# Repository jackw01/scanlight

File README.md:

# A Better Light Source For Scanning Color Negative Film

Left: [scanlight v4](./v4.md), right: [big scanlight](./big.md)

<small>Originally published 2024-08-05, last updated 2026-08-02</small>

## tl;dr

Narrowband trichromatic (RGB) light sources are superior to broadband (white) light for scanning color negative film; there are very good reasons why all commercial film scanners use RGB. ([film scanners were using blue LEDs at least a decade before they would be widely used in consumer products!](https://patents.google.com/patent/JPH09130546A/en?q=(film+scanner+LED)&oq=film+scanner+LED&sort=old)) Scanning film with an RGB light source produces high quality results with minimal post-processing, without the need for specialized software.

### the results

<small>Both scans captured using Fujifilm X-T30. White light scan captured using 95+ CRI 5000K light source. RGB scan captured using custom 450nm+525nm+665nm light source.</small>

## the simplified explanation

Color negative (C-41) film stores an image using cyan, magenta, and yellow dyes. Dyes appear a certain color because they absorb some wavelengths of light; for example, yellow dye mostly absorbs light in the 400-550nm range (which we perceive as violet through green), while allowing other wavelengths (yellow through red) to pass through the film. **These dyes are not intended to produce a human-viewable image, but rather to attenuate certain wavelengths of light for making prints on photosensitive paper.**

White light sources emit light over a broad spectrum of wavelengths. When white light passes through C-41 film, some of these wavelengths are only slightly absorbed by the dyes, which means that these wavelengths aren't useful for recovering the information stored in the individual dye layers - for example, the 580-620nm band (yellow through red-orange light) is mostly transmitted through the film, with a small amount being absorbed by both the magenta and cyan dye layers.

The quality of white light sources is measured with CRI, which represents how well a light source reproduces the true color of a set of standardized color swatches. CRI is effectively a weighted average of how much light a light source emits across different parts of the visible light spectrum, and only a few of these parts matter when it comes to extracting information from color film. **CRI doesn't take into account the deep red (>630nm) and deep blue (<480nm) parts of the spectrum, so as a result, many high-CRI LEDs don't emit much light at these wavelengths, which happen to be where the yellow and cyan dyes absorb the most light.**

<small>note: Standardized scores that take into account these wavelength bands at the edges of the visible spectrum do exist (R9 and R12), but are not readily provided by all LED manufacturers.</small>

With darkroom printing, this is not an issue, as RA-4 color print paper (and motion picture print film) are, by design, most sensitive to specific bands of wavelengths that avoid the crosstalk regions between the dye layers in negative film, and the paper is exposed with an incandescent light source with a smooth emission spectrum across the entire visible range (400-700nm) and beyond.

What about scanning film with a digital camera? Digital camera sensors are designed to capture light in a way that allows for a faithful reproduction of the colors that humans would perceive (this is a gross oversimplification.) C-41 film was *not* designed to be directly viewed by humans.

Not only is the camera sensitive to wavelengths of light that are effectively ignored by RA-4 paper, there is significant crosstalk between the color channel sensitivities of digital camera sensors: light in the ~580-600nm range is seen roughly equally by the red and green channels, and light in the ~480-500nm range is seen by both the green and blue channels.

The red channel of the scan will contain not just information from the red-blocking cyan dye, but also the green-blocking magenta dye. The green channel will contain information from all three dye layers. Additionally, the overall light transmission of C-41 film is heavily biased towards yellow and orange wavelengths due to the orange mask and the relatively large gap between the magenta and cyan dye absorption peaks, which means that **a lot** of light gets through that interferes with both the red and green channels in the camera sensor without carrying much useful information about the colors stored in the film.

<small>note: the orange color of C-41 film is often misunderstood to be the color of the plastic film base, or an orange tint evenly applied over the whole image. It is actually a corrective mask made up of blue- and green-blocking positive images which compensate for deficiencies in the red-sensing and green-sensing layers of the film. For a good explanation of how this works, see [this article](https://observablehq.com/@dorskyee/understanding-color-film). In practice, this means that less-exposed parts of the negative let through disproportionately more yellow, orange, and red light.</small>

So if you scan color negative film with white light, you can't just invert the colors and expect a good result. You need to do some math to try to recover the individual dye layers of the film from ambiguous input data. This can't be done in standard image editing software, which is why dedicated software for negative conversion exists. The level of crosstalk on each channel depends heavily on both the emission spectra of the light source and the spectral sensitivity of the camera, so the conversion process needs to be either calibrated, manually adjusted until it looks “right”, or deduced by the processing software with varying degrees of accuracy. The color depth of the resulting positive image will be relatively low because much of the information recorded by the camera is effectively useless yellow-orange light that has passed through the film without being significantly attenuated by any of the dyes.

To avoid these issues, (almost?) all commercial negative film scanners use a trichromatic narrowband light source with red, green, and blue LEDs to minimize crosstalk between the dye layers in the film and the color channels on the image sensor, and some use monochrome sensors to eliminate sensor crosstalk entirely. When doing it this way, no guesswork is needed to recover a usable image and it's really as simple as inverting the color channels and setting the color balance and black/white points. There is still some crosstalk between camera sensor channels, but now that the light source emits light in three narrow, independently controllable wavelength bands, it can be easily measured and compensated for, or it can be avoided completely by imaging the red, green, and blue channels separately.

### what light source works the best?

When considering the limitations of digital camera sensors, the ideal wavelengths are >650nm for red and <450nm for blue, as shown in the diagram above. Ideally, the green wavelength is 540-560nm to match the absorption peak of the magenta dye, but LEDs in that range are just not practical (see FAQ below for more details), and the standard 525nm works very well.

The next best alternative is to use general purpose RGB LEDs, which typically use 620-630nm for red and 460-480nm for blue. The results will not be the absolute best possible, but will still be far better than with white light. The Fuji Frontier SP3000, a popular professional scanner, uses 630nm for red and 465nm for blue ([source](https://discuss.pixls.us/t/input-color-profile-to-use-for-negatives/20271/13)), but it does not have to contend with the color channel sensitivity of a typical digital camera - it has a monochrome image sensor and combines three exposures taken with red, green, and blue light.

To get the best possible results, I designed my own custom RGB light sources using 665nm red and 455nm blue LEDs. More information on the designs can be found [here (scanlight v4)](./v4.md) and [here (big scanlight)](./big.md). Both light sources allow for individual control of the red, green, and blue channels via a web app. Color balance can be adjusted for single-exposure scanning, and the light can automatically switch colors and trigger a camera to simplify the process of capturing separate exposures for each channel.

All design files for the light sources and film carriers, both current and older versions, can be downloaded from the [GitHub repository](https://github.com/jackw01/scanlight/).

### more sample scans

All scans were processed in [NegPy](https://github.com/marcinz606/NegPy), leaving all settings at the default values. The RGB scans were scanned as **single exposures with all color channels** and sensor crosstalk calibration was applied. The groups of four negatives were scanned and manually processed together in order to demonstrate how the light source affects the overall look of the scans rather than to show a subjectively ideal edit for each photo.

<p align="center"><small>Kodak Ektar 100 (left: white light, right: narrowband RGB light)</small></p>

<p align="center"><small>Fuji 200 (left: white light, right: narrowband RGB light)</small></p>

<p align="center"><small>Kodak Ektar 100 (left: white light, right: narrowband RGB light)</small></p>

<p align="center"><small>Kodak Vision3 500T (left: white light, right: narrowband RGB light)</small></p>

<p align="center"><small>Fuji 200 (left: white light, right: narrowband RGB light)</small></p>

<p align="center"><small>Fuji 200 (left: white light, right: narrowband RGB light)</small></p>

### recommended reading, if you're curious

* Edward J Giorgianni and Thomas E Madden, *Digital Color Management: Encoding Solutions, 2nd Edition*
* Robert L Shanebrook, *Making Kodak Film*

## part 2: responses to frequent questions and comments

<small>Updated 2026-08-02</small>

#### how should i process my scans?
As of 2026, free and open-source film scan processing software exists ([NegPy](https://github.com/marcinz606/NegPy)) which produces excellent results with little effort when inverting single-exposure RGB scans. NegPy uses a processing pipeline which emulates the RA-4 printing process, and supports flat-field correction and automatic merging of trichromatic (separate exposures for red, green, and blue) scans. I would highly recommend this to anyone who is looking to start scanning film at home or is having difficulty with their current processing workflow.

Using software specifically designed for processing white light scans (e.g. Negative Lab Pro) to process RGB scans may give suboptimal results. It's also possible to get good results without using any specialized software, by manually inverting your scans in photo editing software as described below. Manual inversion is much easier with RGB scans than with white light scans, but it still takes more effort than NegPy, and compensating for camera sensor crosstalk may be difficult depending on which image editing software you use.

#### but can't i just edit the white light scan to look like the RGB scan?
You can't get the exact same colors as the RGB scan by adjusting the white balance or individual color channels of a white light scan. This is physically impossible because the light interacted with the film in a fundamentally different way in the white light scan vs. the RGB scan before it was reduced to three bins of wavelengths approximately representing red, green, and blue by the camera sensor; some of the color information stored in the film is lost in this process.

#### but i keep seeing/hearing that using RGB light results in oversaturation or hue shifts
Increasing saturation is often done on purpose to produce a visually striking and not entirely accurate demonstration of why RGB is better (in practice, the differences in color reproduction are more subtle once saturation is equalized), or is the result of processing RGB scans with processing workflows intended to produce normal-looking results with white light scans. No one is saying you can’t adjust saturation in post, or use processing software that produces less-saturated results. Hue shifts are a result of using a processing workflow that doesn't compensate for camera sensor channel crosstalk, and should be a complete non-issue if using the sensor calibration tool in NegPy.

<p align="center"><small>From left to right: RGB scan without sensor calibration (note blue-to-cyan and orange-to-magenta shifts); RGB scan with sensor calibration; Noritsu HS-1800 lab scan</small></p>

#### but the colors in the sample scans still don't look good to me / the colors don't look the way i think film should look
Getting the desired colors from C-41 film, whether by darkroom printing or scanning and editing, has always involved some level of manual adjustment. It is also worth noting that our collective idea of how film is supposed to look is often influenced by highly edited or low-quality scans; old, faded prints; or even software emulations. **Photography is art, and as such it has always involved making subjective decisions about how images should look; all photos are interpretations of raw data and it's up to the photographer to decide what interpretation looks best.** The best starting point for editing is a scan that represents the image data stored in the dye layers of the film with maximum dynamic range and minimal crosstalk.

#### won't this make all film look the same?
Scanning film with RGB light does not neutralize the differences in the "look" of different films; actually, it should produce results that are closer to the intended look of the film when printed on RA-4 paper. The differences in look come from differences in the film's sensitivity to light during exposure and chemical reactions that affect how the dyes are formed during development, not the absorption characteristics of the dyes themselves.

#### should i capture three separate exposures for each color channel?
You can either capture a single image with the red, green, and blue channels on at the same time or capture separate images for each color and merge them later. Both methods can produce satisfactory results. The latter approach has the potential for more technically accurate colors as it eliminates any chance of crosstalk between color channels, but takes significantly more work than capturing a single RGB image which can be processed directly.

When capturing red, green, and blue at the same time, the severity of crosstalk depends heavily on the spectral response of the camera's image sensor and camera manufacturer's color profile, and it may not even be noticeable in many cases. Crosstalk typically manifests as consistent color shifts (usually, reds appearing too pink or greens appearing too yellow,) and can usually be resolved by post-processing with software that supports a crosstalk matrix or RGB primary calibration, such as NegPy (open-source) or Lightroom.

#### how should i adjust the red/green/blue channel levels on the light source?
The red, green, and blue channels on the light source should be adjusted to maximize how much of the camera's dynamic range is utilized on all three color channels. To do this, set the camera white balance to neutral/5000K and adjust the light source so that the histogram peaks on each channel become aligned when the camera is viewing the light through an unexposed, developed piece of film. The deep red (~650nm) and deep blue (~450nm) wavelengths used for RGB scanning are near the edge of what most Bayer-filter image sensors are sensitive to, so some cameras will be significantly more sensitive to one of these wavelengths than others. Therefore, the optimal settings will differ between camera manufacturers and models.

#### should i use narrowband light for scanning color positive (slide) film?
Some people have had success using an adjustable RGB light source for recovering faded slides, but I would not recommend using a narrowband light source for scanning slides that are in good condition. The results I have seen so far are not promising compared to using white light, as colors are typically oversaturated and pink, red, and orange hues become indistinguishable from each other. This likely all comes down to the fact that color positive film is designed to reproduce colors naturally when viewed with a broad-spectrum light source. Any high CRI (95+) white light source should work well. There is some debate over the ideal color temperature: the majority of slide projectors used halogen bulbs with a 3000K-3500K color temperature, but some will argue that a 5000K color temperature should be used instead (this seems to be because Fujifilm datasheets recommend viewing with a ISO 3664 compliant viewer, which historically would have used specialized 5000K high-CRI fluorescent tubes as a light source). I haven't seen a side-by-side comparison, but I would assume that the difference in results would be very subtle or nonexistent if the white balance is corrected when editing the scans.

#### does light source / color matter for scanning black and white film?
No. White and narrowband light sources work equally well for scanning B&W film.

#### what are your thoughts on film carriers?
I have received quite a few emails echoing the sentiment that the film carriers on the market now are generally overpriced for what they are, and there seems to be little correlation between price and user experience. Most film carriers made for DSLR scanning guide the film through a narrow slot with an S-shaped curve on each end to keep it flat. For 35mm film, this seems to generally work well, and based on the reviews and comments I have seen I am not convinced that out of the many film carriers using this design, any perform significantly better than the others. For 120 film, the s-curve design struggles with film flatness when scanning the end frames on cut pieces of film, or if the film is curled across its width. There are a few alternative designs out there that should be able to provide superior film flatness in this case, but I haven't yet seen a thorough quantitative comparison of these. Some of these also involve rough 3D-printed parts coming into direct contact with the film emulsion, which doesn't seem ideal.

##### what about full-border scanning?
Film carriers that allow full-border scanning tend to be significantly worse at keeping the film flat and handling curled film, except for ones that hold the film against glass or acrylic, but those come with other issues (high cost, difficulty keeping the glass clean, Newton's rings, etc.)

#### what lens should i use?
[This list](https://www.pixl-latr.com/how-good-a-macro-lens-do-you-really-need-for-dslr-mirrorless-camera-scanning/) is generally a good starting point. The Micro-Nikkor 55mm f/2.8 AI is my personal recommendation; it outperforms many modern lenses in field flatness, corner-to-corner sharpness, and chromatic aberration, and it is very affordable.

I would **not** recommend low-cost third-party macro lenses like the TTArtisan 40mm f/2.8 Macro or 7artisans 60mm f/2.8 Macro II. While the build quality of these lenses is excellent and they generally have superior contrast to vintage lenses due to better optical coatings, in my experience they cannot match the top tiers of lenses in the above list in corner-to-corner sharpness and lack of chromatic aberration. I would also recommend against using extension tubes with modern lenses; this tends to result in field curvature and other aberrations which can be quite severe depending on the lens.

#### does brightness enhancing film actually work? should i use it?
Brightness enhancing film (BEF) does indeed work to make diffuse light sources more directional, but this can cause other issues. Collimated light makes the image on the film appear slightly sharper, but also exaggerates the appearance of dust and scratches. Depending on the relative positioning of the light source, film, and lens; and type of lens used; grid or moiré patterns may appear due to the structure of the brightness enhancing film and vignetting may occur or become more pronounced. BEF also tends to be difficult to keep clean of dust and fingerprints.

#### what about using an LCD/OLED display as the light source?
OLED displays do contain separate red, green, and blue emitters, but they typically have broader emission spectra than inorganic LEDs, and the red and blue peak wavelengths tend to be closer to 620nm and 470nm respectively. They will produce results with less crosstalk than a white light source, but not as good as RGB LEDs.

Older LCD displays generally emit white light that has been filtered through red, green, and blue filters and recombined. The results will depend on the emission spectrum of the exact display used, and will generally be no better than a white light source. Newer high-gamut LCDs (especially quantum dot LED LCDs) use backlight LEDs with special phosphors designed to emit in narrower bands than typical white LEDs, so they should in theory work as well as OLED.

#### 540-560nm appears to be the ideal green wavelength, why use 525nm?
LEDs in the 540-560nm range are impractical for most uses due to poor efficiency and thus are not widely available. Some GaP green LEDs exist which have peak emission at 555nm, but they are extremely inefficient, requiring hundreds to match the light output of a single 2835 mid-power InGaN LED. Some manufacturers do offer 530-535nm wavelength bins of their InGaN mid-power green LEDs, but these are difficult to source as they are commercially undesirable due to lower efficiency. Applications where a "true green" or "lime green" color is desired usually now use phosphor-converted LEDs, which are very efficient but are suboptimal for film scanning as they output light over a much broader band of wavelengths (60-100nm FWHM vs 15-30nm for direct green LEDs.)

##### how did old film scanners get ~540nm?
They either used cold-cathode fluorescent lamps with phosphors tuned to emit at the desired wavelengths, or used InGaN green LEDs from a higher wavelength bin. These have become increasingly hard to find as manufacturing processes have become more consistent and the industry has settled on ~525nm as the standard green wavelength for lighting and display applications. On the other hand, mid- and high-power ~450nm deep blue and ~660nm deep red LEDs have stayed available alongside their more common ~470nm and ~620nm counterparts due to increased demand, mostly in horticultural applications.

#### why does big scanlight have infrared LEDs?
The IR LEDs are for dust removal – the dyes in color negative film transmit infrared light, but dust does not. By capturing a separate IR image with an IR-sensitive camera, dust particles on the image can be easily located and inpainted. I originally added the LEDs for a specific customer who uses a specialized industrial camera and custom software processing pipeline to do this. As of June 2026, the only free/open-source software I know of that can automate this process is [NegPy](https://github.com/marcinz606/NegPy), although I haven't yet tested it with output from big scanlight.

#### will there be a desktop app for scanlight?
There are no plans for a desktop app right now, since the easiest way to make one by far is to just repackage a web app as a desktop app and there is little to be gained by doing this. It is possible to install the app as a progressive web app on most platforms, which will make it appear as a desktop app and allow it to be used without an internet connection.

#### what if i want to manually invert my scans?
It's definitely much easier to do this with narrowband scans than white light scans, but I still recommend using NegPy due to its automatic analysis and camera sensor calibration abilities.

##### 1. scan
Scan all frames as RAW using fixed white balance and exposure. Exposure should be set such that none of the color channels are clipping.
##### 2. import
Import scans into image editing software. Use a linear RAW profile. Apply lens corrections and use Lens Cast Calibration in Capture One or Flat-Field Correction in Lightroom to compensate for any unevenness in the light source if necessary.
##### 3. d-min balance
Neutralize the color of the minimum density (unexposed) areas of one negative by adjusting the red, green, and blue channel max levels.
##### 4. inversion
Invert the black and white points using the Levels or Curves tool and apply an s-shaped tone curve to adjust contrast. Use the brightness/gamma/Levels tool midpoint controls to adjust the overall scene brightness without affecting the black and white points.
##### 5. fine tuning
Apply the same adjustments to all scans from the same roll of film. Manually fine-tune the black and white points and brightness/gamma for all scans.
##### 6. crosstalk compensation
Use either the primary calibration panel in Lightroom, or the color tools in Capture One (more difficult), correct any hue shifts in the scans. Since hue shifts occur due to crosstalk between camera sensor channels in the light source emission bands, not any property of the film itself, this adjustment should be performed across a broad sample of images and saved for future use.

## license

The PCB schematic, layout, and Gerber files and the 3D CAD files for this project are released under the [CERN Open Hardware Licence Version 2 - Weakly Reciprocal](https://choosealicense.com/licenses/cern-ohl-w-2.0/) (CERN-OHL-W V2). Software and firmware are released under the MIT License. The text and illustrations in this article may not be reproduced without permission.

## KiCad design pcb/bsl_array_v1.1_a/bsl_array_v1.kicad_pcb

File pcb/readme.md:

# PCB revision reference

Revisions of each PCB are listed below in reverse chronological order. Older revisions may have known issues and should not be built - see the errata.md file in each revision's folder.

| product name                         | part number | revision date | folder            | status                     |
| ------------------------------------ | ----------- | ------------- | ----------------- | -------------------------- |
| **scanlight v4 (rev. b)**            | 26a901b     | 2026-06-28    | sl_v4_b           | **latest (in production)** |
| **big scanlight v1.1 LED array**     | 26b901a     | 2026-10-08    | bsl_array_v1.1_a  | **latest (in production)** |
| **big scanlight v1.1 LED driver**    | 26b902a     | 2026-10-08    | bsl_driver_v1.1_a | **latest (in production)** |
| scanlight v4 (rev. a)                | 26a901a     | 2026-03-29    | sl_v4_a           | discontinued               |
| big scanlight v1 (rev. c) LED array  | 25d901c     | 2026-01-20    | bsl_array_v1_b    | end of life                |
| big scanlight v1 (rev. b) LED driver | 25d902b     | 2026-01-20    | bsl_driver_v1_b   | end of life                |
| big scanlight v1 (rev. b) LED array  | 25d901b     | 2025-11-09    | bsl_array_v1_a    | discontinued               |
| big scanlight v1 (rev. a) LED driver | 25d902a     | 2025-11-09    | bsl_driver_v1_a   | discontinued               |

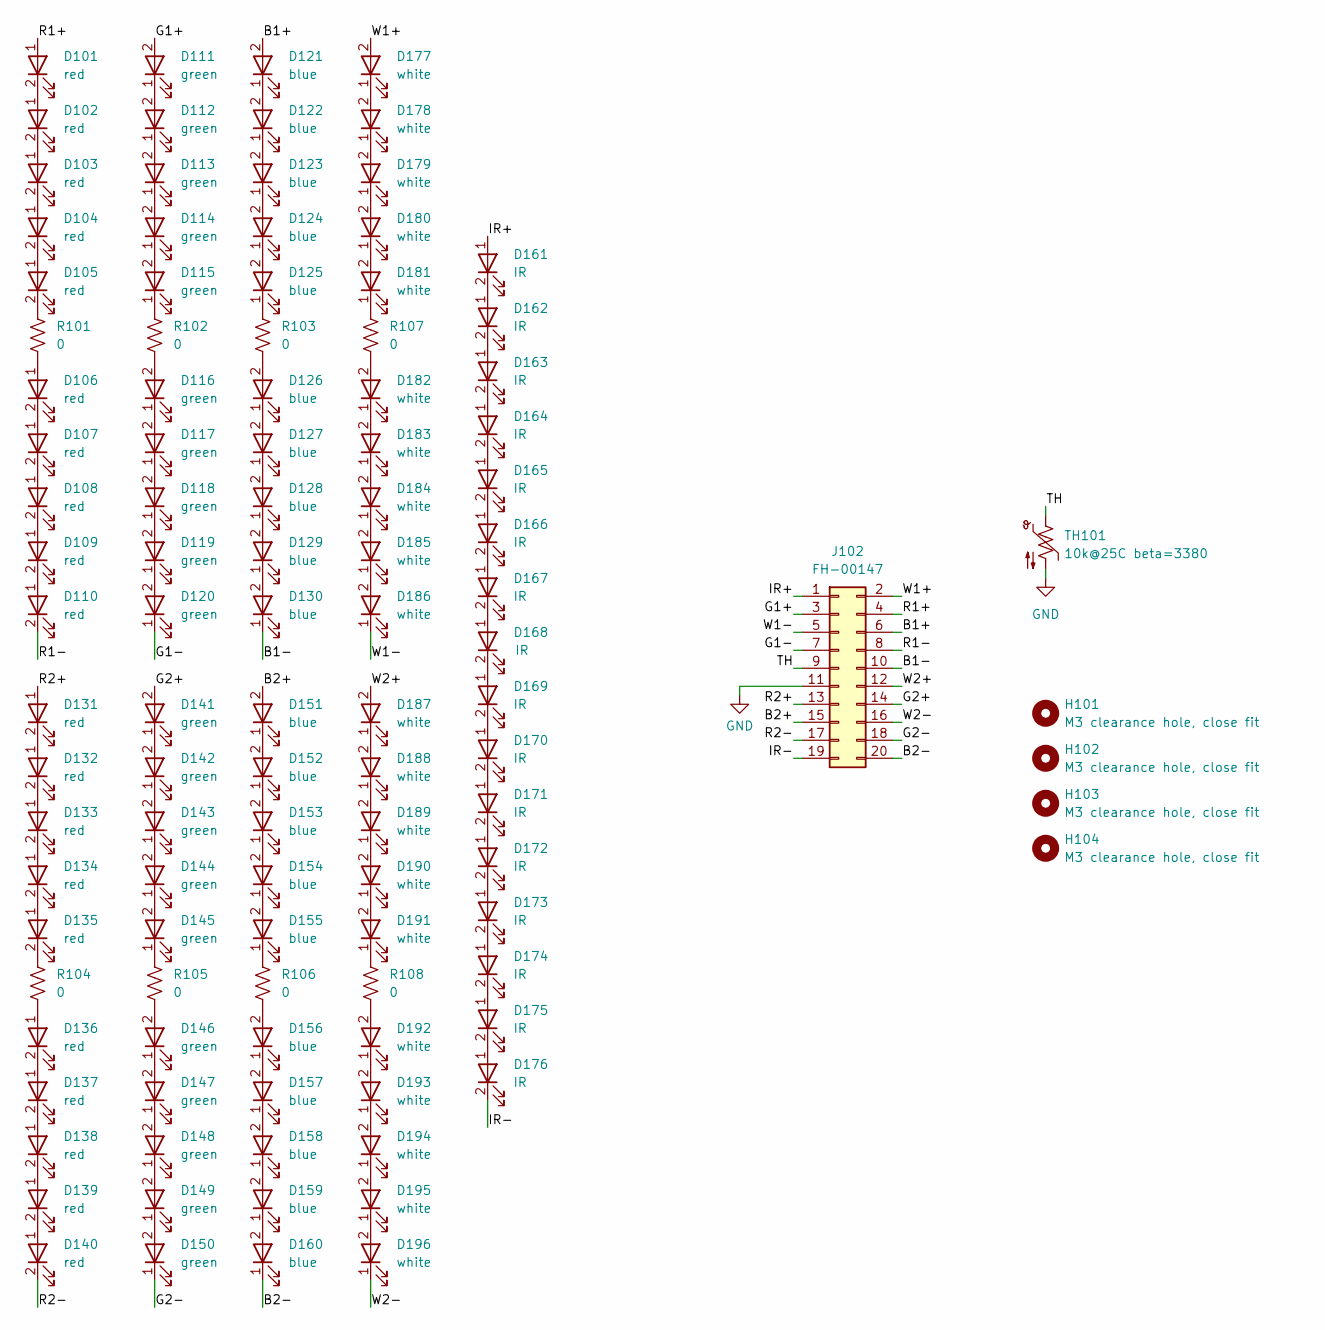
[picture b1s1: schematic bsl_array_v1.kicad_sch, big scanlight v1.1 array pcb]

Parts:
D101, D102, D103, D104, D105, D106, D107, D108, D109, D110, D131, D132, D133, D134, D135, D136, D137, D138, D139, D140: red; LED_2835_Reversed_Red; MPN HL-AS-2835D15FC-S1-08-PCT-ZW-P6; LCSC C49435764
D111, D112, D113, D114, D115, D116, D117, D118, D119, D120, D141, D142, D143, D144, D145, D146, D147, D148, D149, D150: green; LED_2835; MPN TJ-S2835UG5W8TLC2G-A5; LCSC C440451
D121, D122, D123, D124, D125, D126, D127, D128, D129, D130, D151, D152, D153, D154, D155, D156, D157, D158, D159, D160: blue; LED_2835; MPN TJ-S2835UG5W8TLC6B-A5; LCSC C440452
D161, D162, D163, D164, D165, D166, D167, D168, D169, D170, D171, D172, D173, D174, D175, D176: IR; LED_2835_Reversed_Red; MPN P2835P1IRS7G12 850nm; LCSC C22466172
D177, D178, D179, D180, D181, D182, D183, D184, D185, D186, D187, D188, D189, D190, D191, D192, D193, D194, D195, D196: white; LED_2835; MPN HL-AM-2835H421W-S1-08-HR6-3SDCM(5000K); LCSC C55616349
H101, H102, H103, H104: M3 clearance hole, close fit; MountingHole_3.2mm_M3_Mask
J102: FH-00147; PinSocket_2x10_P2.00mm_Vertical_SMD; MPN FH-00147; LCSC C2685091
R101, R102, R103, R104, R105, R106, R107, R108: 0; R_1206_3216Metric; MPN 1206W4F0000T5E; LCSC C17888
TH101: 10k@25C beta=3380; R_0603_1608Metric; MPN NCP18XH103F03RB; LCSC C13564

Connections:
/B1+: D121.2 (A), J102.6
/B1-: D130.1 (K), J102.10
/B2+: D151.2 (A), J102.15
/B2-: D160.1 (K), J102.20
/G1+: D111.2 (A), J102.3
/G1-: D120.1 (K), J102.7
/G2+: D141.2 (A), J102.14
/G2-: D150.1 (K), J102.18
/IR+: D161.1 (A), J102.1
/IR-: D176.2 (K), J102.19
/R1+: D101.1 (A), J102.4
/R1-: D110.2 (K), J102.8
/R2+: D131.1 (A), J102.13
/R2-: D140.2 (K), J102.17
/TH: J102.9, TH101.1
/W1+: D177.2 (A), J102.2
/W1-: D186.1 (K), J102.5
/W2+: D187.2 (A), J102.12
/W2-: D196.1 (K), J102.16
GND: J102.11, TH101.2
unnamed: D101.2 (K), D102.1 (A)
unnamed: D102.2 (K), D103.1 (A)
unnamed: D103.2 (K), D104.1 (A)
unnamed: D104.2 (K), D105.1 (A)
unnamed: D105.2 (K), R101.1
unnamed: D106.1 (A), R101.2
unnamed: D106.2 (K), D107.1 (A)
unnamed: D107.2 (K), D108.1 (A)
unnamed: D108.2 (K), D109.1 (A)
unnamed: D109.2 (K), D110.1 (A)
unnamed: D111.1 (K), D112.2 (A)
unnamed: D112.1 (K), D113.2 (A)
unnamed: D113.1 (K), D114.2 (A)
unnamed: D114.1 (K), D115.2 (A)
unnamed: D115.1 (K), R102.1
unnamed: D116.2 (A), R102.2
unnamed: D116.1 (K), D117.2 (A)
unnamed: D117.1 (K), D118.2 (A)
unnamed: D118.1 (K), D119.2 (A)
unnamed: D119.1 (K), D120.2 (A)
unnamed: D121.1 (K), D122.2 (A)
unnamed: D122.1 (K), D123.2 (A)
unnamed: D123.1 (K), D124.2 (A)
unnamed: D124.1 (K), D125.2 (A)
unnamed: D125.1 (K), R103.1
unnamed: D126.2 (A), R103.2
unnamed: D126.1 (K), D127.2 (A)
unnamed: D127.1 (K), D128.2 (A)
unnamed: D128.1 (K), D129.2 (A)
unnamed: D129.1 (K), D130.2 (A)
unnamed: D131.2 (K), D132.1 (A)
unnamed: D132.2 (K), D133.1 (A)
unnamed: D133.2 (K), D134.1 (A)
unnamed: D134.2 (K), D135.1 (A)
unnamed: D135.2 (K), R104.1
unnamed: D136.1 (A), R104.2
unnamed: D136.2 (K), D137.1 (A)
unnamed: D137.2 (K), D138.1 (A)
unnamed: D138.2 (K), D139.1 (A)
unnamed: D139.2 (K), D140.1 (A)
unnamed: D141.1 (K), D142.2 (A)
unnamed: D142.1 (K), D143.2 (A)
unnamed: D143.1 (K), D144.2 (A)
unnamed: D144.1 (K), D145.2 (A)
unnamed: D145.1 (K), R105.1
unnamed: D146.2 (A), R105.2
unnamed: D146.1 (K), D147.2 (A)
unnamed: D147.1 (K), D148.2 (A)
unnamed: D148.1 (K), D149.2 (A)
unnamed: D149.1 (K), D150.2 (A)
unnamed: D151.1 (K), D152.2 (A)
unnamed: D152.1 (K), D153.2 (A)
unnamed: D153.1 (K), D154.2 (A)
unnamed: D154.1 (K), D155.2 (A)
unnamed: D155.1 (K), R106.1
unnamed: D156.2 (A), R106.2
unnamed: D156.1 (K), D157.2 (A)
unnamed: D157.1 (K), D158.2 (A)
unnamed: D158.1 (K), D159.2 (A)
unnamed: D159.1 (K), D160.2 (A)
unnamed: D161.2 (K), D162.1 (A)
unnamed: D162.2 (K), D163.1 (A)
unnamed: D163.2 (K), D164.1 (A)
unnamed: D164.2 (K), D165.1 (A)
unnamed: D165.2 (K), D166.1 (A)
unnamed: D166.2 (K), D167.1 (A)
unnamed: D167.2 (K), D168.1 (A)
unnamed: D168.2 (K), D169.1 (A)
unnamed: D169.2 (K), D170.1 (A)
unnamed: D170.2 (K), D171.1 (A)
unnamed: D171.2 (K), D172.1 (A)
unnamed: D172.2 (K), D173.1 (A)
unnamed: D173.2 (K), D174.1 (A)
unnamed: D174.2 (K), D175.1 (A)
unnamed: D175.2 (K), D176.1 (A)
unnamed: D177.1 (K), D178.2 (A)
unnamed: D178.1 (K), D179.2 (A)
unnamed: D179.1 (K), D180.2 (A)
unnamed: D180.1 (K), D181.2 (A)
unnamed: D181.1 (K), R107.1
unnamed: D182.2 (A), R107.2
unnamed: D182.1 (K), D183.2 (A)
unnamed: D183.1 (K), D184.2 (A)
unnamed: D184.1 (K), D185.2 (A)
unnamed: D185.1 (K), D186.2 (A)
unnamed: D187.1 (K), D188.2 (A)
unnamed: D188.1 (K), D189.2 (A)
unnamed: D189.1 (K), D190.2 (A)
unnamed: D190.1 (K), D191.2 (A)
unnamed: D191.1 (K), R108.1
unnamed: D192.2 (A), R108.2
unnamed: D192.1 (K), D193.2 (A)
unnamed: D193.1 (K), D194.2 (A)
unnamed: D194.1 (K), D195.2 (A)
unnamed: D195.1 (K), D196.2 (A)

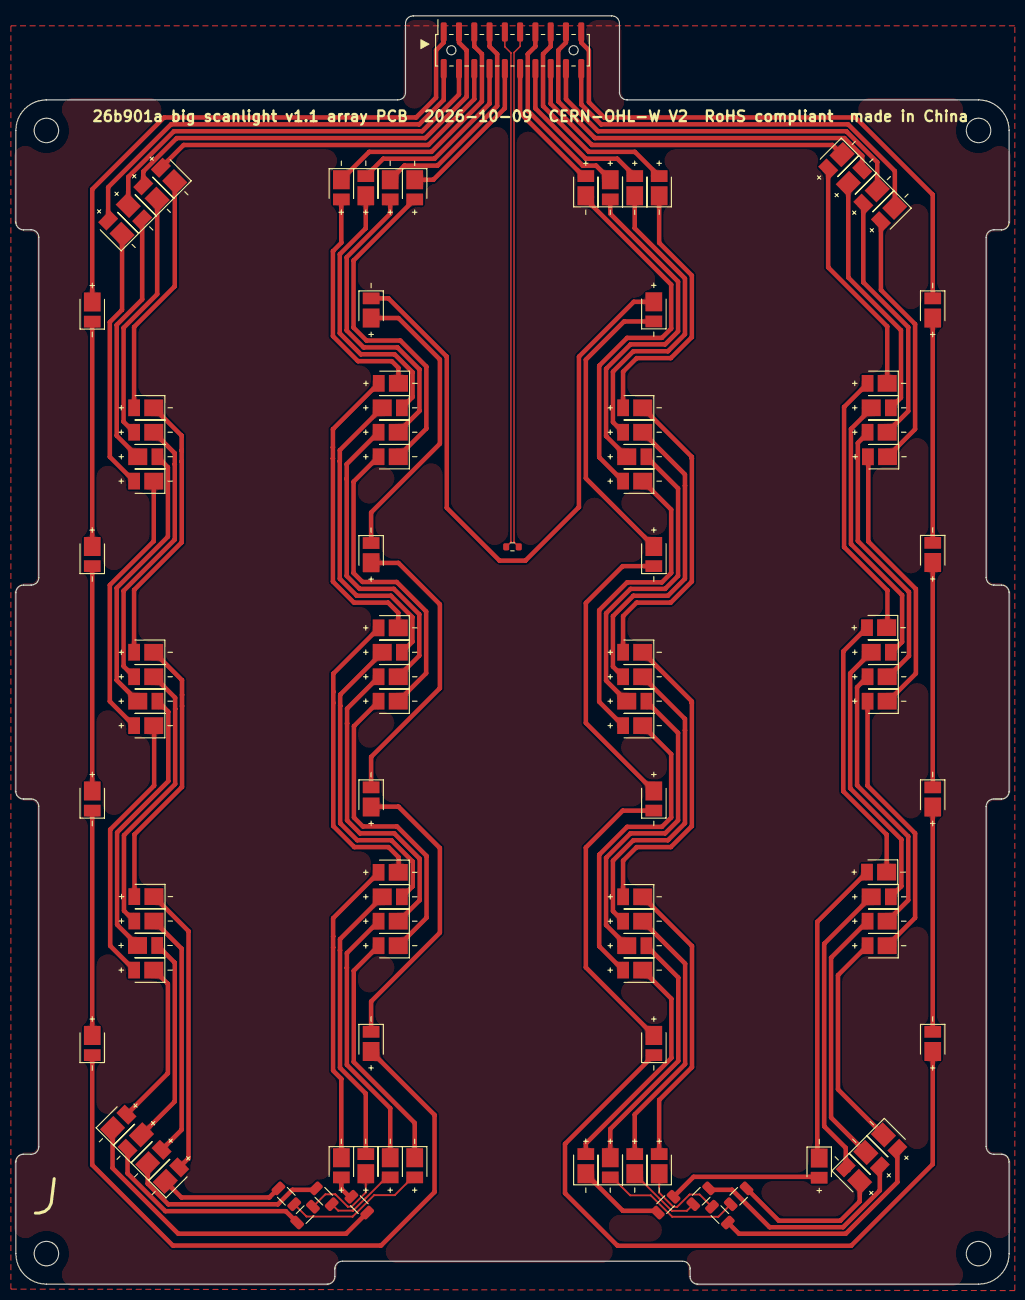
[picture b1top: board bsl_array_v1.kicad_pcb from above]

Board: 2 copper layers, 130.0 x 166.0 mm, 110 parts (0 on the bottom side), 115 nets.

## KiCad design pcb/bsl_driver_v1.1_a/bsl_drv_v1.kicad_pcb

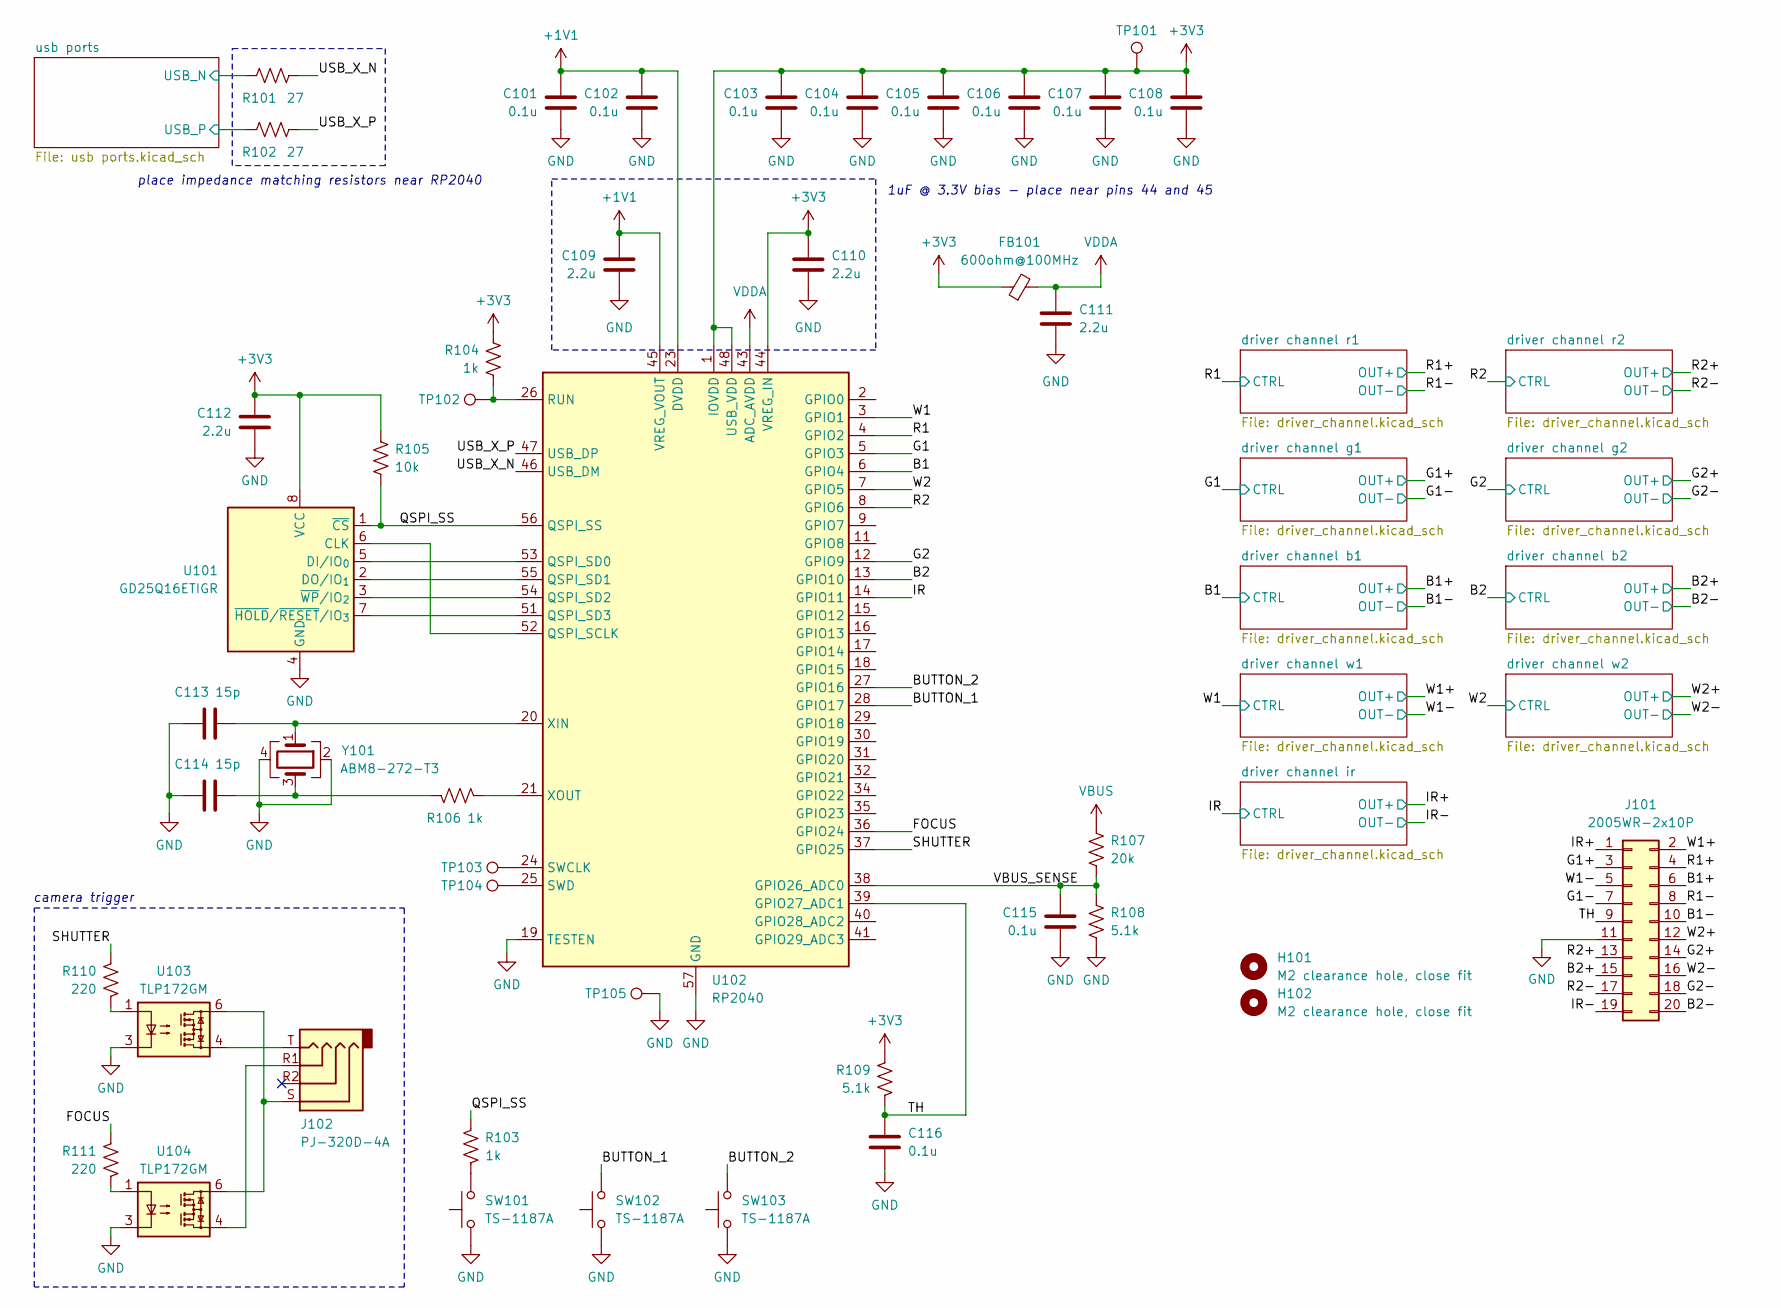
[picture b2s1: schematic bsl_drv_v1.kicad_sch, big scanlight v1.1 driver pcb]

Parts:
C101, C102, C103, C104, C105, C106, C107, C108, C115, C116: 0.1u; C_0402_1005Metric; MPN CL05B104KB54PNC; LCSC C307331
C109, C110, C111, C112: 2.2u; C_0402_1005Metric; MPN CL05A225MQ5NSNC; LCSC C12530
C113, C114: 15p; C_0402_1005Metric; MPN 0402CG150J500NT; LCSC C1548
FB101: 600ohm@100MHz; L_0603_1608Metric; MPN GZ1608D601TF; LCSC C1002
H101, H102: M2 clearance hole, close fit; MountingHole_2.2mm_M2_Mask_tight
J101: 2005WR-2x10P; PinHeader_2x10_P2.00mm_Horizontal; MPN 2005WR-2x10P; LCSC C6837626
J102: PJ-320D-4A; Jack_3.5mm_KoreanHropartsElec_PJ-320D-4A_Horizontal; MPN PJ-320D-4A; LCSC C95562
R101, R102: 27; R_0402_1005Metric; MPN 0402WGF270JTCE; LCSC C25100
R103, R104, R106: 1k; R_0402_1005Metric; MPN 0402WGF1001TCE; LCSC C11702
R105: 10k; R_0402_1005Metric; MPN 0402WGF1002TCE; LCSC C25744
R107: 20k; R_0402_1005Metric; MPN 0402WGF2002TCE; LCSC C25765
R108, R109: 5.1k; R_0402_1005Metric; MPN 0402WGF5101TCE; LCSC C25905
R110, R111: 220; R_0402_1005Metric; MPN 0402WGF2200TCE; LCSC C25091
SW101, SW102, SW103: TS-1187A; SW_PTS526; MPN TS-1187A-B-A-B; LCSC C318884
TP101, TP102, TP103, TP104, TP105: TestPoint; TestPoint_Pad_D1.0mm
U101: GD25Q16ETIGR; SOIC-8_3.9x4.9mm_P1.27mm; MPN GD25Q16ETIGR; LCSC C2904431
U102: RP2040; QFN-56-1EP_7x7mm_P0.4mm_EP3.2x3.2mm; MPN RP2040; LCSC C2040
U103, U104: TLP172GM; Toshiba_SOIC-4-6_4.4x3.6mm_P1.27mm; MPN TLP172GM; LCSC C261926
Y101: ABM8-272-T3; Crystal_SMD_Abracon_ABM8G-4Pin_3.2x2.5mm; MPN ABM8-272-T3; LCSC C20625731

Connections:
+1V1: C101.1, C102.1, C109.1, U102.23 (DVDD), U102.45 (VREG_VOUT), U102.50 (DVDD)
+3V3: C103.1, C104.1, C105.1, C106.1, C107.1, C108.1, C110.1, C112.1, FB101.1, R104.2, R105.1, R109.1, TP101.1 (1_1), U101.8 (VCC), U102.1 (IOVDD), U102.10 (IOVDD), U102.22 (IOVDD), U102.33 (IOVDD), U102.42 (IOVDD), U102.44 (VREG_IN), U102.48 (USB_VDD), U102.49 (IOVDD); also elsewhere on the board
/B1: U102.6 (GPIO4); also elsewhere on the board
/B1+: J101.6; also elsewhere on the board
/B1-: J101.10; also elsewhere on the board
/B2: U102.13 (GPIO10); also elsewhere on the board
/B2+: J101.15; also elsewhere on the board
/B2-: J101.20; also elsewhere on the board
/BUTTON_1: SW102.2, U102.28 (GPIO17)
/BUTTON_2: SW103.2, U102.27 (GPIO16)
/FOCUS: R111.1, U102.36 (GPIO24)
/G1: U102.5 (GPIO3); also elsewhere on the board
/G1+: J101.3; also elsewhere on the board
/G1-: J101.7; also elsewhere on the board
/G2: U102.12 (GPIO9); also elsewhere on the board
/G2+: J101.14; also elsewhere on the board
/G2-: J101.18; also elsewhere on the board
/IR: U102.14 (GPIO11); also elsewhere on the board
/IR+: J101.1; also elsewhere on the board
/IR-: J101.19; also elsewhere on the board
/QSPI_SS: R103.2, R105.2, U101.1 (~CS), U102.56 (QSPI_SS)
/R1: U102.4 (GPIO2); also elsewhere on the board
/R1+: J101.4; also elsewhere on the board
/R1-: J101.8; also elsewhere on the board
/R2: U102.8 (GPIO6); also elsewhere on the board
/R2+: J101.13; also elsewhere on the board
/R2-: J101.17; also elsewhere on the board
/SHUTTER: R110.1, U102.37 (GPIO25)
/TH: C116.1, J101.9, R109.2, U102.39 (GPIO27_ADC1)
/USB_X_N: R101.1, U102.46 (USB_DM)
/USB_X_P: R102.2, U102.47 (USB_DP)
/VBUS_SENSE: C115.1, R107.1, R108.1, U102.38 (GPIO26_ADC0)
/W1: U102.3 (GPIO1); also elsewhere on the board
/W1+: J101.2; also elsewhere on the board
/W1-: J101.5; also elsewhere on the board
/W2: U102.7 (GPIO5); also elsewhere on the board
/W2+: J101.12; also elsewhere on the board
/W2-: J101.16; also elsewhere on the board
/usb ports/USB_N: R101.2; also elsewhere on the board
/usb ports/USB_P: R102.1; also elsewhere on the board
GND: C101.2, C102.2, C103.2, C104.2, C105.2, C106.2, C107.2, C108.2, C109.2, C110.2, C111.2, C112.2, C113.1, C114.1, C115.2, C116.2, J101.11, R108.2, SW101.1, SW102.1, SW103.1, TP105.1 (1_1), U101.4 (GND), U102.19 (TESTEN), U102.57 (GND), U103.3, U104.3, Y101.2, Y101.4; also elsewhere on the board
unnamed: C114.2, R106.1, Y101.3
unnamed: J102.R1, U104.4
unnamed: J102.S, U103.6, U104.6
unnamed: J102.T, U103.4
unnamed: R103.1, SW101.2
unnamed: R110.2, U103.1
unnamed: R111.2, U104.1
unnamed: U101.6 (CLK), U102.52 (QSPI_SCLK)
unnamed: U101.5 (DI/IO_{0}), U102.53 (QSPI_SD0)
unnamed: U101.2 (DO/IO_{1}), U102.55 (QSPI_SD1)
unnamed: U101.7 (~HOLD/~RESET/IO_{3}), U102.51 (QSPI_SD3)
unnamed: U101.3 (~WP/IO_{2}), U102.54 (QSPI_SD2)
unnamed: R104.1, TP102.1 (1_1), U102.26 (RUN)
unnamed: TP103.1 (1_1), U102.24 (SWCLK)
unnamed: TP104.1 (1_1), U102.25 (SWD)
unnamed: C113.2, U102.20 (XIN), Y101.1
unnamed: R106.2, U102.21 (XOUT)
VBUS: R107.2; also elsewhere on the board
VDDA: C111.1, FB101.2, U102.43 (ADC_AVDD)

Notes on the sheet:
place impedance matching resistors near RP2040
1uF @ 3.3V bias - place near pins 44 and 45
camera trigger

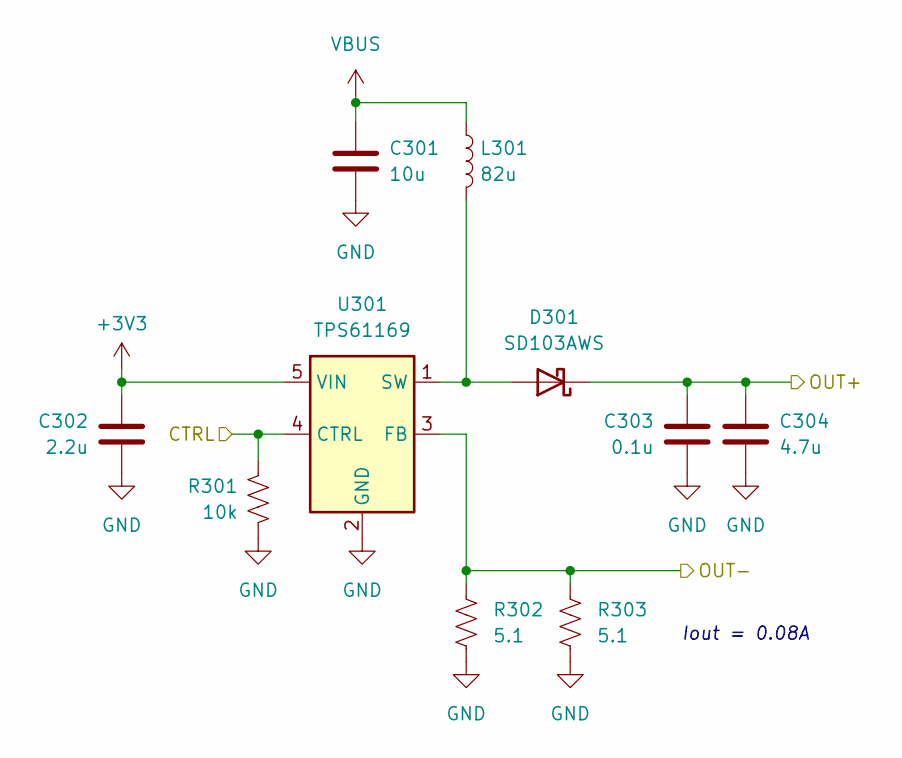
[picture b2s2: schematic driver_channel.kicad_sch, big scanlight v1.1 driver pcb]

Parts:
C301: 10u; C_0805_2012Metric; MPN CL21A106KAYNNNE; LCSC C15850
C302: 2.2u; C_0402_1005Metric; MPN CL05A225MQ5NSNC; LCSC C12530
C303: 0.1u; C_0402_1005Metric; MPN CL05B104KB54PNC; LCSC C307331
C304: 4.7u; C_1206_3216Metric; MPN 1206B475K500NT; LCSC C29823
D301: SD103AWS; D_SOD-323; MPN SD103AWS; LCSC C7420360
L301: 82u; L_Sunlord_SWPA6028S; MPN FNR6028S820MT; LCSC C168047
R301: 10k; R_0402_1005Metric; MPN 0402WGF1002TCE; LCSC C25744
R302, R303: 5.1; R_0603_1608Metric; MPN TD03H5R10FT; LCSC C2961388
U301: TPS61169; SOT-353_SC-70-5_BSL_verified; MPN TPS61169DCKR; LCSC C71045

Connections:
+3V3: C302.1, U301.5 (VIN); also elsewhere on the board
/R1: R301.1, U301.4 (CTRL); also elsewhere on the board
/R1+: C303.1, C304.1, D301.1 (K); also elsewhere on the board
/R1-: R302.1, R303.1, U301.3 (FB); also elsewhere on the board
GND: C301.2, C302.2, C303.2, C304.2, R301.2, R302.2, R303.2, U301.2 (GND); also elsewhere on the board
unnamed: D301.2 (A), L301.2, U301.1 (SW)
VBUS: C301.1, L301.1; also elsewhere on the board

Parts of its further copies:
C401, C501, C601, C701, C801, C901, C1001, C1101: 10u; C_0805_2012Metric; MPN CL21A106KAYNNNE; LCSC C15850
C402, C502, C602, C702, C802, C902, C1002, C1102: 2.2u; C_0402_1005Metric; MPN CL05A225MQ5NSNC; LCSC C12530
C403, C503, C603, C703, C803, C903, C1003, C1103: 0.1u; C_0402_1005Metric; MPN CL05B104KB54PNC; LCSC C307331
C404, C504, C604, C704, C804, C904, C1004, C1104: 4.7u; C_1206_3216Metric; MPN 1206B475K500NT; LCSC C29823
D401, D501, D601, D701, D801, D901, D1001, D1101: SD103AWS; D_SOD-323; MPN SD103AWS; LCSC C7420360
L401, L501, L601, L701, L801, L901, L1001, L1101: 82u; L_Sunlord_SWPA6028S; MPN FNR6028S820MT; LCSC C168047
R401, R501, R601, R701, R801, R901, R1001, R1101: 10k; R_0402_1005Metric; MPN 0402WGF1002TCE; LCSC C25744
R402, R403, R502, R503, R602, R603, R702, R703, R802, R803, R902, R903, R1002, R1003, R1102, R1103: 5.1; R_0603_1608Metric; MPN TD03H5R10FT; LCSC C2961388
U401, U501, U601, U701, U801, U901, U1001, U1101: TPS61169; SOT-353_SC-70-5_BSL_verified; MPN TPS61169DCKR; LCSC C71045

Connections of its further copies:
+3V3: C402.1, C502.1, C602.1, C702.1, C802.1, C902.1, C1002.1, C1102.1, U401.5 (VIN), U501.5 (VIN), U601.5 (VIN), U701.5 (VIN), U801.5 (VIN), U901.5 (VIN), U1001.5 (VIN), U1101.5 (VIN); also elsewhere on the board
/B1: R701.1, U701.4 (CTRL); also elsewhere on the board
/B1+: C703.1, C704.1, D701.1 (K); also elsewhere on the board
/B1-: R702.1, R703.1, U701.3 (FB); also elsewhere on the board
/B2: R801.1, U801.4 (CTRL); also elsewhere on the board
/B2+: C803.1, C804.1, D801.1 (K); also elsewhere on the board
/B2-: R802.1, R803.1, U801.3 (FB); also elsewhere on the board
/G1: R501.1, U501.4 (CTRL); also elsewhere on the board
/G1+: C503.1, C504.1, D501.1 (K); also elsewhere on the board
/G1-: R502.1, R503.1, U501.3 (FB); also elsewhere on the board
/G2: R601.1, U601.4 (CTRL); also elsewhere on the board
/G2+: C603.1, C604.1, D601.1 (K); also elsewhere on the board
/G2-: R602.1, R603.1, U601.3 (FB); also elsewhere on the board
/IR: R901.1, U901.4 (CTRL); also elsewhere on the board
/IR+: C903.1, C904.1, D901.1 (K); also elsewhere on the board
/IR-: R902.1, R903.1, U901.3 (FB); also elsewhere on the board
/R2: R401.1, U401.4 (CTRL); also elsewhere on the board
/R2+: C403.1, C404.1, D401.1 (K); also elsewhere on the board
/R2-: R402.1, R403.1, U401.3 (FB); also elsewhere on the board
/W1: R1001.1, U1001.4 (CTRL); also elsewhere on the board
/W1+: C1003.1, C1004.1, D1001.1 (K); also elsewhere on the board
/W1-: R1002.1, R1003.1, U1001.3 (FB); also elsewhere on the board
/W2: R1101.1, U1101.4 (CTRL); also elsewhere on the board
/W2+: C1103.1, C1104.1, D1101.1 (K); also elsewhere on the board
/W2-: R1102.1, R1103.1, U1101.3 (FB); also elsewhere on the board
GND: C401.2, C402.2, C403.2, C404.2, C501.2, C502.2, C503.2, C504.2, C601.2, C602.2, C603.2, C604.2, C701.2, C702.2, C703.2, C704.2, C801.2, C802.2, C803.2, C804.2, C901.2, C902.2, C903.2, C904.2, C1001.2, C1002.2, C1003.2, C1004.2, C1101.2, C1102.2, C1103.2, C1104.2, R401.2, R402.2, R403.2, R501.2, R502.2, R503.2, R601.2, R602.2, R603.2, R701.2, R702.2, R703.2, R801.2, R802.2, R803.2, R901.2, R902.2, R903.2, R1001.2, R1002.2, R1003.2, R1101.2, R1102.2, R1103.2, U401.2 (GND), U501.2 (GND), U601.2 (GND), U701.2 (GND), U801.2 (GND), U901.2 (GND), U1001.2 (GND), U1101.2 (GND); also elsewhere on the board
unnamed: D401.2 (A), L401.2, U401.1 (SW)
unnamed: D501.2 (A), L501.2, U501.1 (SW)
unnamed: D601.2 (A), L601.2, U601.1 (SW)
unnamed: D701.2 (A), L701.2, U701.1 (SW)
unnamed: D801.2 (A), L801.2, U801.1 (SW)
unnamed: D901.2 (A), L901.2, U901.1 (SW)
unnamed: D1001.2 (A), L1001.2, U1001.1 (SW)
unnamed: D1101.2 (A), L1101.2, U1101.1 (SW)
VBUS: C401.1, C501.1, C601.1, C701.1, C801.1, C901.1, C1001.1, C1101.1, L401.1, L501.1, L601.1, L701.1, L801.1, L901.1, L1001.1, L1101.1; also elsewhere on the board

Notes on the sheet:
Iout = 0.08A

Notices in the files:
pcb/bsl_array_v1.1_a/bsl_array_v1.kicad_pcb:
26b901a big scanlight v1.1 array PCB  2026-10-09  CERN-OHL-W V2  RoHS compliant  made in China
pcb/sl_v4_a/sl_v4.kicad_pcb:
made in China  RoHS compliant  CERN-OHL-W V2
